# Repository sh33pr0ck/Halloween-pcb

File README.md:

# Halloween-pcb

Building a project to automate some Halloween decorations.

Based on the Raspberry Pi Shield template.

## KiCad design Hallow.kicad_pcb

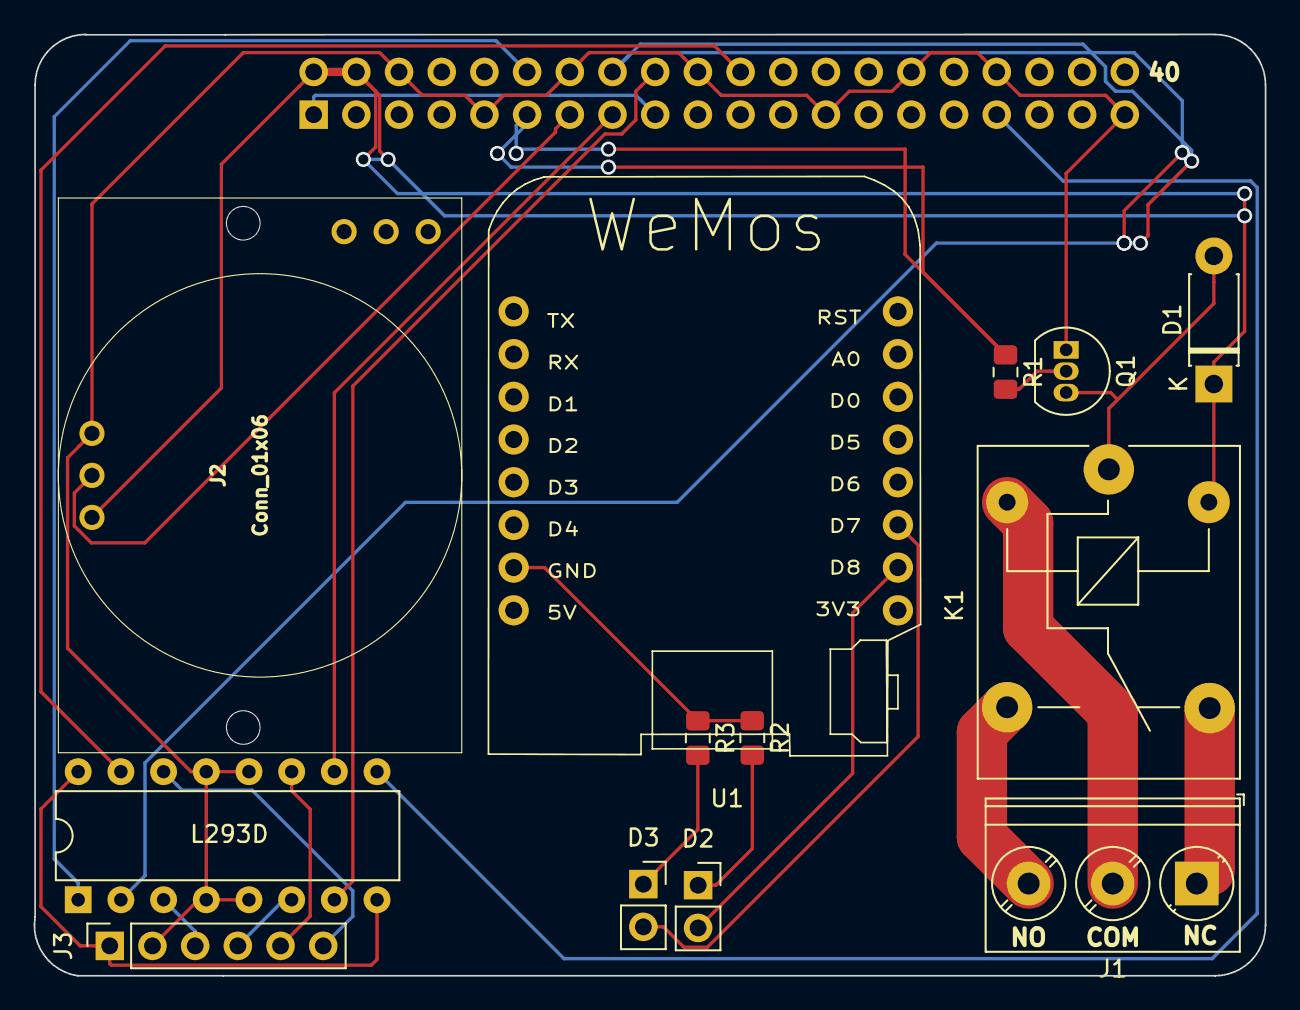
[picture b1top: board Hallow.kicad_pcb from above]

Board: 2 copper layers, 73.2 x 56.0 mm, 14 parts (1 on the bottom side), 26 nets.

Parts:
D1: D; D_DO-41_SOD81_P7.62mm_Horizontal
D2, D3: LED; PinSocket_1x02_P2.54mm_Vertical
J1: Screw_Terminal_01x03; TerminalBlock_Phoenix_PT-1,5-3-5.0-H_1x03_P5.00mm_Horizontal
J2: Conn_01x06; HC-SR501
J3: Conn_01x06; PinSocket_1x06_P2.54mm_Vertical
K1: G5Q-1; Relay_SPDT_SANYOU_SRD_Series_Form_C
L293D: L293D; DIP-16_W7.62mm
P1: Conn_02x20_Odd_Even; PinSocket_2x20_P2.54mm_Vertical
Q1: 2N3904; TO-92_Inline
R1, R2, R3: R_US; R_0805_2012Metric_Pad1.15x1.40mm_HandSolder
U1: WeMos_mini; D1_mini_board

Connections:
+3V3: P1.1, P1.17
+5V: D1.1, J2.6, K1.5, P1.2, P1.4
/GPIO13(PWM1): L293D.9, P1.33
/GPIO17(GEN0): P1.11, R1.1
/GPIO18(GEN1)(PWM0): L293D.1, P1.12
/GPIO22(GEN3): L293D.10, P1.15
/GPIO23(GEN4): L293D.2, P1.16
/GPIO24(GEN5): L293D.7, P1.18
/GPIO25(GEN6): L293D.15, P1.22
/GPIO27(GEN2): J2.5, P1.13
/Out1: J3.3, L293D.3
/Out2: J3.4, L293D.6
/Out3: J3.5, L293D.11
/Out4: J3.6, L293D.14
/RLY1: D1.2, K1.1, Q1.3
/RLY(COM): J1.2, K1.2
/RLY(NC): J1.1, K1.4
/RLY(NO): J1.3, K1.3
/Vcc2: J3.1, L293D.8, L293D.16
/WM_D7: D3.2, U1.14
/WM_D8: D2.2, U1.15
/WM_GND: R2.1, R3.1, U1.2
GND: J2.4, J3.2, L293D.4, L293D.5, L293D.12, L293D.13, P1.6, P1.9, P1.14, P1.20, P1.25, P1.30, P1.34, P1.39, Q1.1
unnamed: D2.1, R2.2
unnamed: D3.1, R3.2
unnamed: Q1.2, R1.2

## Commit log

2018-10-01 ADD Files
2018-10-01 Updated files
2018-10-05 Added Gerbers and added L293D
